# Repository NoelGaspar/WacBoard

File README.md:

# WacBoard
tesis based on wacboard v01

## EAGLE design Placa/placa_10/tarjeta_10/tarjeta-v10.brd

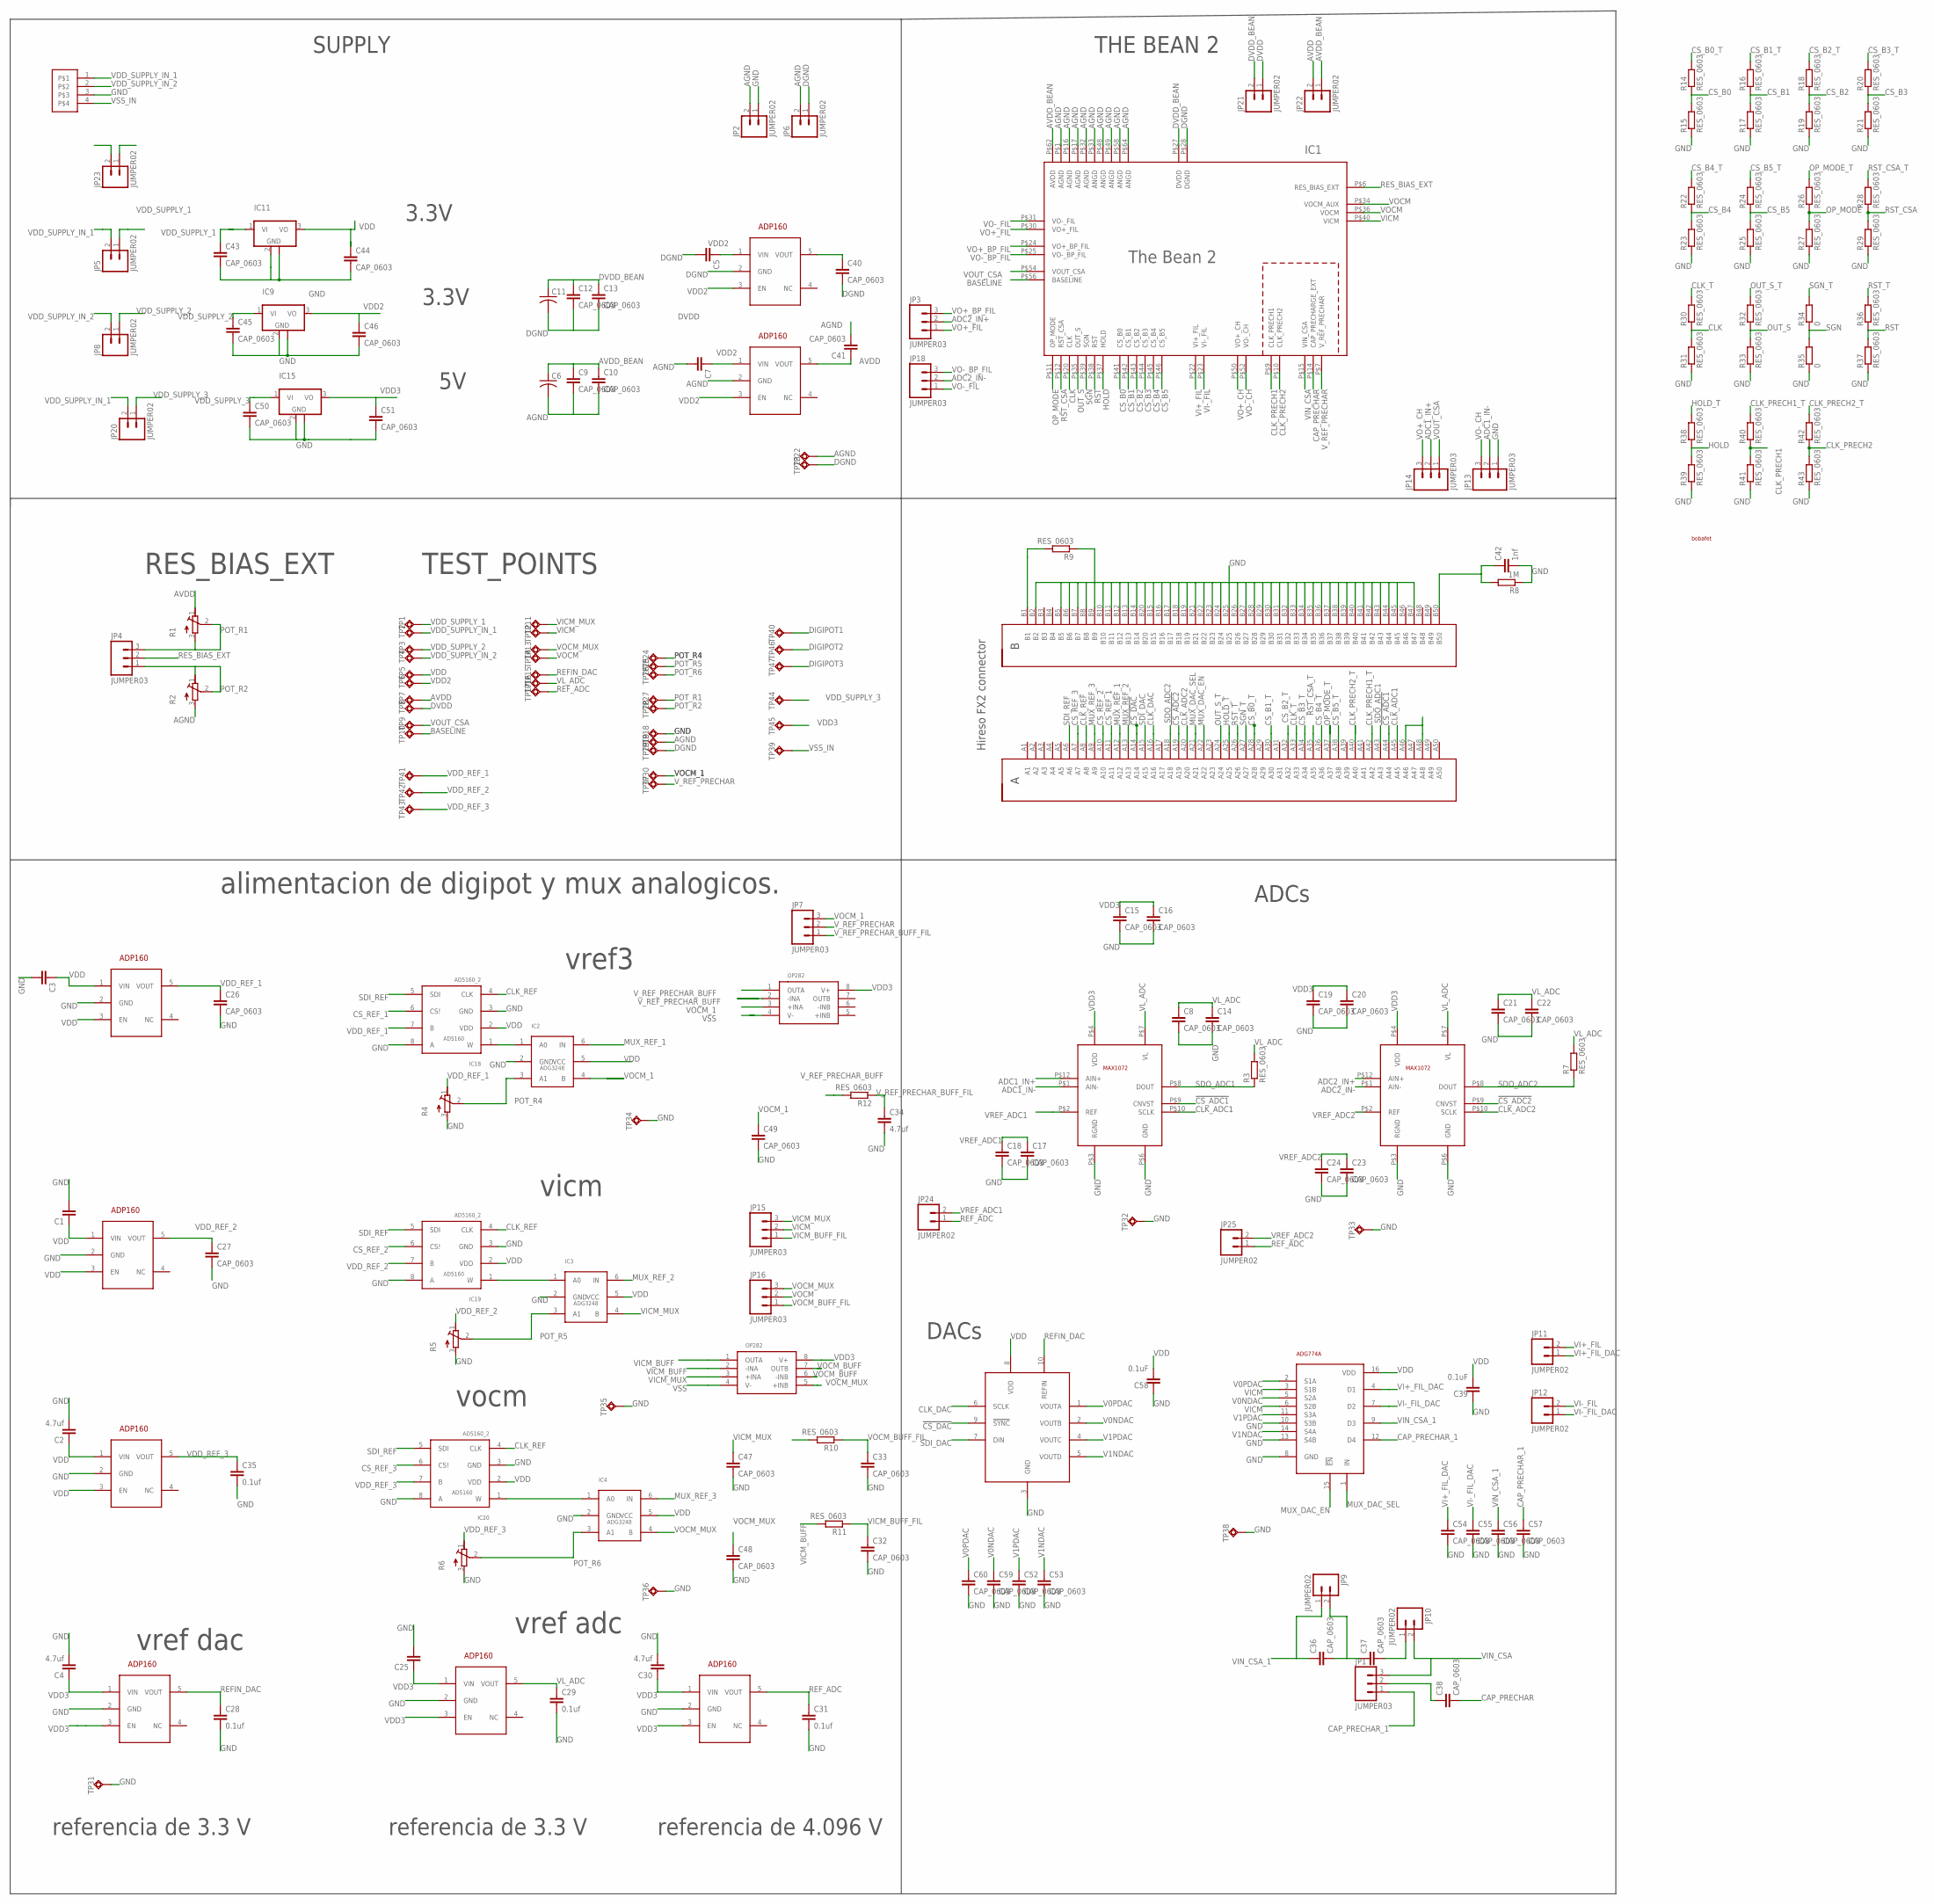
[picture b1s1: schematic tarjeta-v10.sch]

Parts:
C1, C3, C5, C7, C25: CAP_0402; C0402
C2, C4, C30: 4.7uf; C0402
C6, C11: CAP_0805; C0805
C8, C9, C10, C12, C13, C14, C15, C16, C17, C18, C19, C20, C21, C22, C23, C24, C26, C27, C32, C33, C36, C37, C38, C40, C41, C43, C44, C45, C46, C47, C48, C49, C50, C51, C52, C53, C54, C55, C56, C57, C59, C60: CAP_0603; C0603
C28, C29, C31, C35: 0.1uf; C0603
C34: 4.7uf; C0603
C39, C58: 0.1uF; C0603
C42: 1nf; C0603
IC1: THEBEAN2; CQFP64
IC2, IC3, IC4: ADG3248; SC70
IC5, IC6, IC7, IC8, IC10, IC13, IC16, IC17: ADP160; SOT23-5L_2
IC9, IC11, IC15: UA78M; SOT223
IC12, IC14: OP282; SOIC8
IC18, IC19, IC20: AD5160_2; SOT23-8_2
IC21: ADG774A; QSOP16
IC22, IC24: MAX1072; TQFN12
IC23: DAC7554; MSOP10
J1: HIRESO_FX_CONNECTOR; FX2-100S-1.27
JP1, JP3, JP4, JP7, JP13, JP14, JP15, JP16, JP18: JUMPER03; 1X03
JP2, JP5, JP6, JP8, JP9, JP10, JP11, JP12, JP20, JP21, JP22, JP23, JP24, JP25: JUMPER02; 1X02
JP17: JUMPER04; 1X04
R1, R2, R4, R5, R6: TRIMMER_ST5; ST-5EW
R3, R7, R9, R10, R11, R12, R14, R15, R16, R17, R18, R19, R20, R21, R22, R23, R24, R25, R26, R27, R28, R29, R30, R31, R32, R33, R36, R37, R38, R39, R40, R41, R42, R43: RES_0603; R0603
R8: 1M; R0603
R34, R35: 0; R0603
TP1, TP2, TP3, TP4, TP5, TP6, TP7, TP8, TP9, TP10, TP11, TP12, TP13, TP14, TP15, TP16, TP17, TP18, TP19, TP22, TP23, TP24, TP25, TP26, TP27, TP28, TP29, TP30, TP31, TP32, TP33, TP34, TP35, TP36, TP37, TP38, TP39, TP40, TP41, TP42, TP43, TP44, TP45, TP46, TP47: TEST_POINT; TP
U$1: LOGO

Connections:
!CS_ADC1: IC22.P$9 (CNVST), J1.A44
!CS_ADC2: IC24.P$9 (CNVST), J1.A19
!CS_DAC: IC23.9 (!SYNC), J1.A14
ADC1_IN+: IC22.P$12 (AIN+), JP14.2
ADC1_IN-: IC22.P$1 (AIN-), JP13.2
ADC2_IN+: IC24.P$12 (AIN+), JP3.2
ADC2_IN-: IC24.P$1 (AIN-), JP18.2
AGND: C6.2, C7.2, C9.2, C10.2, C41.2, IC1.P$1 (AGND), IC1.P$16 (AGND), IC1.P$17 (AGND), IC1.P$32 (AGND), IC1.P$33 (ANGD), IC1.P$48 (ANGD), IC1.P$49 (ANGD), IC1.P$58 (ANGD), IC1.P$64 (ANGD), IC13.2 (GND), JP2.2, JP6.2, R2.3, TP19.TP, TP22.TP
AVDD: C41.1, IC13.5 (VOUT), JP22.2, R1.1, TP7.TP
AVDD_BEAN: C6.1, C9.1, C10.1, IC1.P$62 (AVDD), JP22.1
BASELINE: IC1.P$56 (BASELINE), TP10.TP
CAP_PRECHAR: C38.2, IC1.P$14 (CAP_PRECHARGE_EXT)
CAP_PRECHAR_1: C57.1, IC21.12 (D4), JP1.1
CLK: IC1.P$20 (CLK), R30.1, R31.2
CLK_ADC1: IC22.P$10 (SCLK), J1.A45
CLK_ADC2: IC24.P$10 (SCLK), J1.A20
CLK_DAC: IC23.6 (SCLK), J1.A16
CLK_PRECH1: IC1.P$9 (CLK_PRECH1), R40.1, R41.2
CLK_PRECH1_T: J1.A42, R40.2
CLK_PRECH2: IC1.P$10 (CLK_PRECH2), R42.1, R43.2
CLK_PRECH2_T: J1.A40, R42.2
CLK_REF: IC18.4 (CLK), IC19.4 (CLK), IC20.4 (CLK), J1.A8
CLK_T: J1.A33, R30.2
CS_B0: IC1.P$41 (CS_B0), R14.1, R15.2
CS_B0_T: J1.A28, R14.2
CS_B1: IC1.P$42 (CS_B1), R16.1, R17.2
CS_B1_T: J1.A30, R16.2
CS_B2: IC1.P$43 (CS_B2), R18.1, R19.2
CS_B2_T: J1.A32, R18.2
CS_B3: IC1.P$44 (CS_B3), R20.1, R21.2
CS_B3_T: J1.A34, R20.2
CS_B4: IC1.P$45 (CS_B4), R22.1, R23.2
CS_B4_T: J1.A36, R22.2
CS_B5: IC1.P$46 (CS_B5), R24.1, R25.2
CS_B5_T: J1.A38, R24.2
CS_REF_1: IC18.6 (CS!), J1.A11
CS_REF_2: IC19.6 (CS!), J1.A10
CS_REF_3: IC20.6 (CS!), J1.A7
DGND: C5.2, C11.2, C12.2, C13.2, C40.2, IC1.P$28 (DGND), IC10.2 (GND), JP6.1, TP23.TP, TP29.TP
DIGIPOT1: IC2.1 (A0), IC18.1 (W), TP40.TP
DIGIPOT2: IC3.1 (A0), IC19.1 (W), TP46.TP
DIGIPOT3: IC4.1 (A0), IC20.1 (W), TP47.TP
DVDD: C40.1, IC10.5 (VOUT), JP21.1, TP8.TP
DVDD_BEAN: C11.1, C12.1, C13.1, IC1.P$27 (DVDD), JP21.2
GND: C1.2, C2.2, C3.2, C4.2, C8.2, C14.2, C15.2, C16.2, C17.2, C18.2, C19.2, C20.2, C21.2, C22.2, C23.2, C24.2, C25.2, C26.2, C27.2, C28.2, C29.2, C30.2, C31.2, C32.2, C33.2, C34.2, C35.2, C39.1, C42.2, C43.2, C44.2, C45.2, C46.2, C47.2, C48.2, C49.2, C50.2, C51.2, C52.2, C53.2, C54.2, C55.2, C56.2, C57.2, C58.1, C59.2, C60.2, IC2.2 (GND), IC3.2 (GND), IC4.2 (GND), IC5.2 (GND), IC6.2 (GND), IC7.2 (GND), IC8.2 (GND), IC9.2 (GND), IC9.4 (GND), IC11.2 (GND), IC11.4 (GND), IC15.2 (GND), IC15.4 (GND), IC16.2 (GND), IC17.2 (GND), IC18.3 (GND), IC18.8 (A), IC19.3 (GND), IC19.8 (A), IC20.3 (GND), IC20.8 (A), IC21.8 (GND), IC21.10 (S3B), IC21.13 (S4B), IC22.P$3 (RGND), IC22.P$6 (GND), IC23.3 (GND), IC24.P$3 (RGND), IC24.P$6 (GND), J1.B2, J1.B5, J1.B6, J1.B7, J1.B8, J1.B9, J1.B10, J1.B11, J1.B12, J1.B13, J1.B14, J1.B15, J1.B16, J1.B17, J1.B18, J1.B19, J1.B20, J1.B21, J1.B22, J1.B23, J1.B24, J1.B25, J1.B26, J1.B27, J1.B28, J1.B29, J1.B30, J1.B31, J1.B32, J1.B33, J1.B34, J1.B35, J1.B36, J1.B37, J1.B38, J1.B39, J1.B40, J1.B41, J1.B42, J1.B43, J1.B44, J1.B45, J1.B47, JP2.1, JP13.1, JP17.3, R4.3, R5.3, R6.3, R8.1, R9.1, R15.1, R17.1, R19.1, R21.1, R23.1, R25.1, R27.1, R29.1, R31.1, R33.1, R35.1, R37.1, R39.1, R41.1, R43.1, TP18.TP, TP31.TP, TP32.TP, TP33.TP, TP34.TP, TP35.TP, TP36.TP, TP38.TP
HOLD: IC1.P$37 (HOLD), R38.1, R39.2
HOLD_T: J1.A25, R38.2
MUX_DAC_EN: IC21.15 (!EN), J1.A22
MUX_DAC_SEL: IC21.1 (IN), J1.A21
MUX_REF_1: IC2.6 (IN), J1.A12
MUX_REF_2: IC3.6 (IN), J1.A13
MUX_REF_3: IC4.6 (IN), J1.A9
unnamed: C36.2, C37.1, JP9.2
unnamed: J1.B1, R9.2
unnamed: C37.2, JP10.1
unnamed: J1.A46, J1.A48
unnamed: C38.1, JP1.2
unnamed: C42.1, J1.B50, R8.2
OP_MODE: IC1.P$11 (OP_MODE), R26.1, R27.2
OP_MODE_T: J1.A37, R26.2
OUT_S: IC1.P$35 (OUT_S), R32.1, R33.2
OUT_S_T: J1.A24, R32.2
POT_R1: JP4.3, R1.2, R1.3, TP27.TP
POT_R2: JP4.1, R2.1, R2.2, TP28.TP
POT_R4: IC2.3 (A1), R4.2, TP24.TP
POT_R5: IC3.3 (A1), R5.2, TP25.TP
POT_R6: IC4.3 (A1), R6.2, TP26.TP
REFIN_DAC: C28.1, IC8.5 (VOUT), IC23.10 (REFIN), TP15.TP
REF_ADC: C31.1, IC17.5 (VOUT), JP24.1, JP25.1, TP17.TP
RES_BIAS_EXT: IC1.P$6 (RES_BIAS_EXT), JP4.2
RST: IC1.P$38 (RST), R36.1, R37.2
RST_CSA: IC1.P$12 (RST_CSA), R28.1, R29.2
RST_CSA_T: J1.A35, R28.2
RST_T: J1.A26, R36.2
SDI_DAC: IC23.7 (DIN), J1.A15
SDI_REF: IC18.5 (SDI), IC19.5 (SDI), IC20.5 (SDI), J1.A6
SDO_ADC1: IC22.P$8 (DOUT), J1.A43, R3.1
SDO_ADC2: IC24.P$8 (DOUT), J1.A18, R7.1
SGN: IC1.P$39 (SGN), R34.1, R35.2
SGN_T: J1.A27, R34.2
V0NDAC: C59.1, IC21.5 (S2A), IC23.2 (VOUTB)
V0PDAC: C60.1, IC21.2 (S1A), IC23.1 (VOUTA)
V1NDAC: C53.1, IC21.14 (S4A), IC23.5 (VOUTD)
V1PDAC: C52.1, IC21.11 (S3A), IC23.4 (VOUTC)
VDD: C1.1, C2.1, C3.1, C39.2, C44.1, C58.2, IC2.5 (VCC), IC3.5 (VCC), IC4.5 (VCC), IC5.1 (VIN), IC5.3 (EN), IC6.1 (VIN), IC6.3 (EN), IC7.1 (VIN), IC7.3 (EN), IC11.3 (VO), IC18.2 (VDD), IC19.2 (VDD), IC20.2 (VDD), IC21.16 (VDD), IC23.8 (VDD), TP5.TP
VDD2: C5.1, C7.1, C46.1, IC9.3 (VO), IC10.1 (VIN), IC10.3 (EN), IC13.1 (VIN), IC13.3 (EN), TP6.TP
VDD3: C4.1, C15.1, C16.1, C19.1, C20.1, C25.1, C30.1, C51.1, IC8.1 (VIN), IC8.3 (EN), IC12.8 (V+), IC14.8 (V+), IC15.3 (VO), IC16.1 (VIN), IC16.3 (EN), IC17.1 (VIN), IC17.3 (EN), IC22.P$4 (VDD), IC24.P$4 (VDD), TP45.TP
VDD_REF_1: C26.1, IC5.5 (VOUT), IC18.7 (B), R4.1, TP41.TP
VDD_REF_2: C27.1, IC6.5 (VOUT), IC19.7 (B), R5.1, TP42.TP
VDD_REF_3: C35.1, IC7.5 (VOUT), IC20.7 (B), R6.1, TP43.TP
VDD_SUPPLY_1: C43.1, IC11.1 (VI), JP5.1, TP1.TP
VDD_SUPPLY_2: C45.1, IC9.1 (VI), JP8.1, TP3.TP
VDD_SUPPLY_3: C50.1, IC15.1 (VI), JP20.1, TP44.TP
VDD_SUPPLY_IN_1: JP5.2, JP17.1, JP20.2, TP2.TP
VDD_SUPPLY_IN_2: JP8.2, JP17.2, TP4.TP
VI+_FIL: IC1.P$22 (VI+_FIL), JP11.2
VI+_FIL_DAC: C54.1, IC21.4 (D1), JP11.1
VI-_FIL: IC1.P$23 (VI-_FIL), JP12.2
VI-_FIL_DAC: C55.1, IC21.7 (D2), JP12.1
VICM: IC1.P$40 (VICM), IC21.3 (S1B), IC21.6 (S2B), JP15.2, TP12.TP
VICM_BUFF: IC12.1 (OUTA), IC12.2 (-INA), R11.2
VICM_BUFF_FIL: C32.1, JP15.1, R11.1
VICM_MUX: C47.1, IC3.4 (B), IC12.3 (+INA), JP15.3, TP11.TP
VIN_CSA: IC1.P$15 (VIN_CSA), JP1.3, JP10.2
VIN_CSA_1: C36.1, C56.1, IC21.9 (D3), JP9.1
VL_ADC: C8.1, C14.1, C21.1, C22.1, C29.1, IC16.5 (VOUT), IC22.P$7 (VL), IC24.P$7 (VL), R3.2, R7.2, TP16.TP
VO+_BP_FIL: IC1.P$24 (VO+_BP_FIL), JP3.3
VO+_CH: IC1.P$50 (VO+_CH), JP14.3
VO+_FIL: IC1.P$30 (VO+_FIL), JP3.1
VO-_BP_FIL: IC1.P$25 (VO-_BP_FIL), JP18.3
VO-_CH: IC1.P$52 (VO-_CH), JP13.3
VO-_FIL: IC1.P$31 (VO-_FIL), JP18.1
VOCM: IC1.P$34 (VOCM_AUX), IC1.P$36 (VOCM), JP16.2, TP14.TP
VOCM_1: C49.1, IC2.4 (B), IC14.3 (+INA), JP7.3, TP30.TP
VOCM_BUFF: IC12.6 (-INB), IC12.7 (OUTB), R10.2
VOCM_BUFF_FIL: C33.1, JP16.1, R10.1
VOCM_MUX: C48.1, IC4.4 (B), IC12.5 (+INB), JP16.3, TP13.TP
VOUT_CSA: IC1.P$54 (VOUT_CSA), JP14.1, TP9.TP
VREF_ADC1: C17.1, C18.1, IC22.P$2 (REF), JP24.2
VREF_ADC2: C23.1, C24.1, IC24.P$2 (REF), JP25.2
VSS: IC12.4 (V-), IC14.4 (V-), JP23.1
VSS_IN: JP17.4, JP23.2, TP39.TP
V_REF_PRECHAR: IC1.P$7 (V_REF_PRECHAR), JP7.2, TP37.TP
V_REF_PRECHAR_BUFF: IC14.1 (OUTA), IC14.2 (-INA), R12.2
V_REF_PRECHAR_BUFF_FIL: C34.1, JP7.1, R12.1

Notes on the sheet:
vicm
vocm
alimentacion de digipot y mux analogicos.
RES_BIAS_EXT
ADCs
SUPPLY
THE BEAN 2
DACs
TEST_POINTS
vref3
vref adc
vref dac
referencia de 3.3 V
referencia de 4.096 V
3.3V

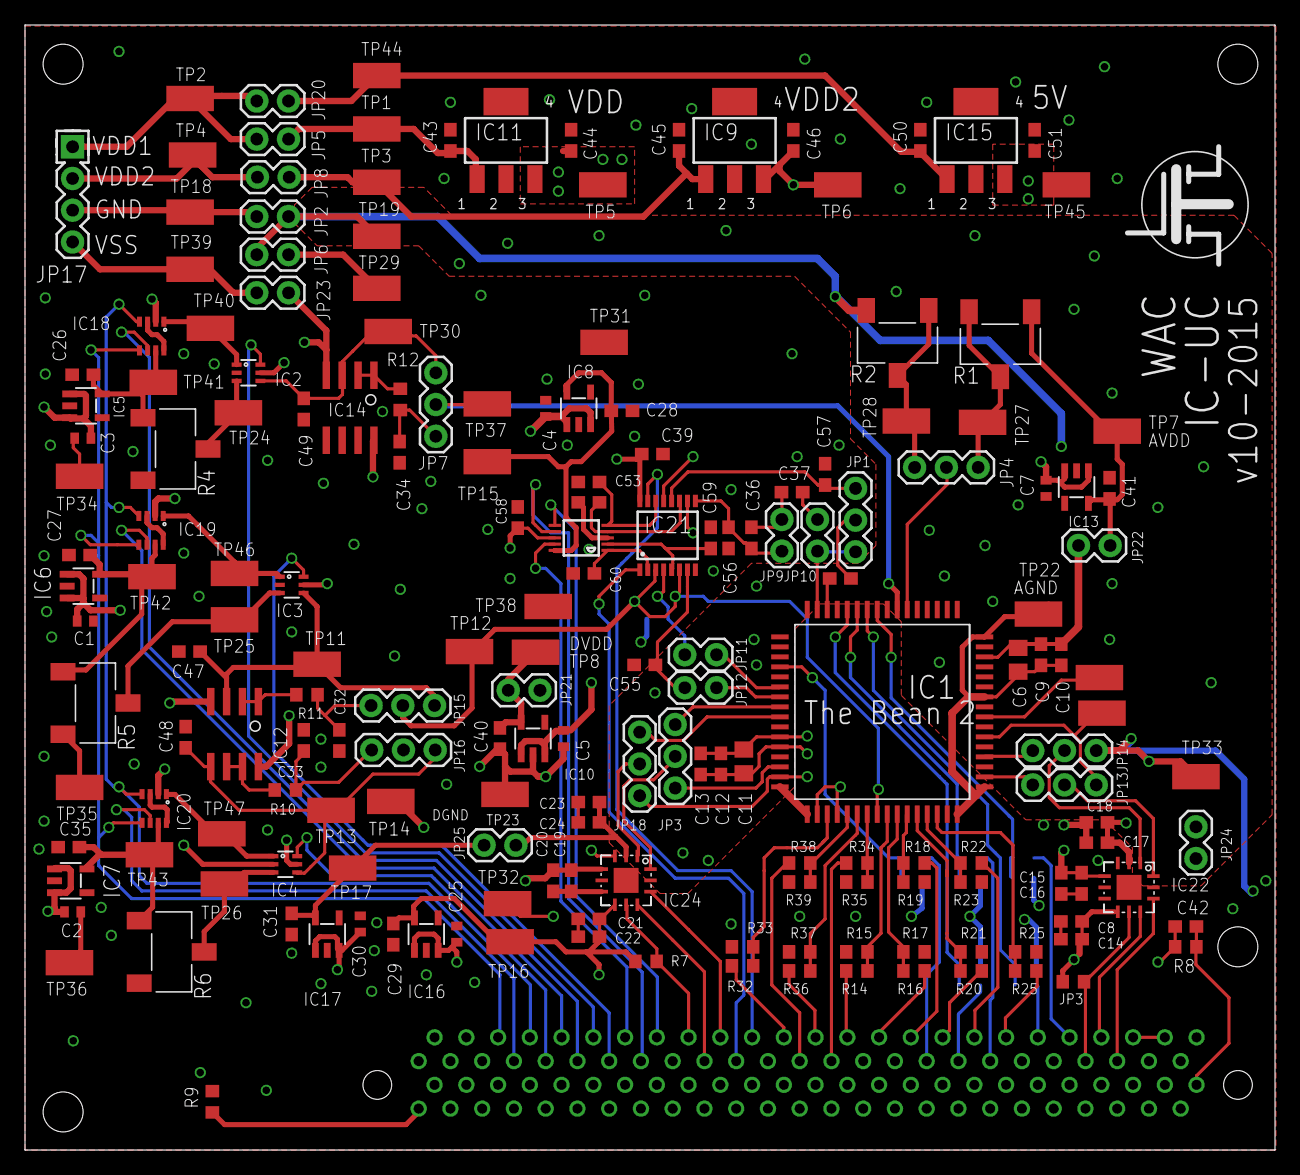
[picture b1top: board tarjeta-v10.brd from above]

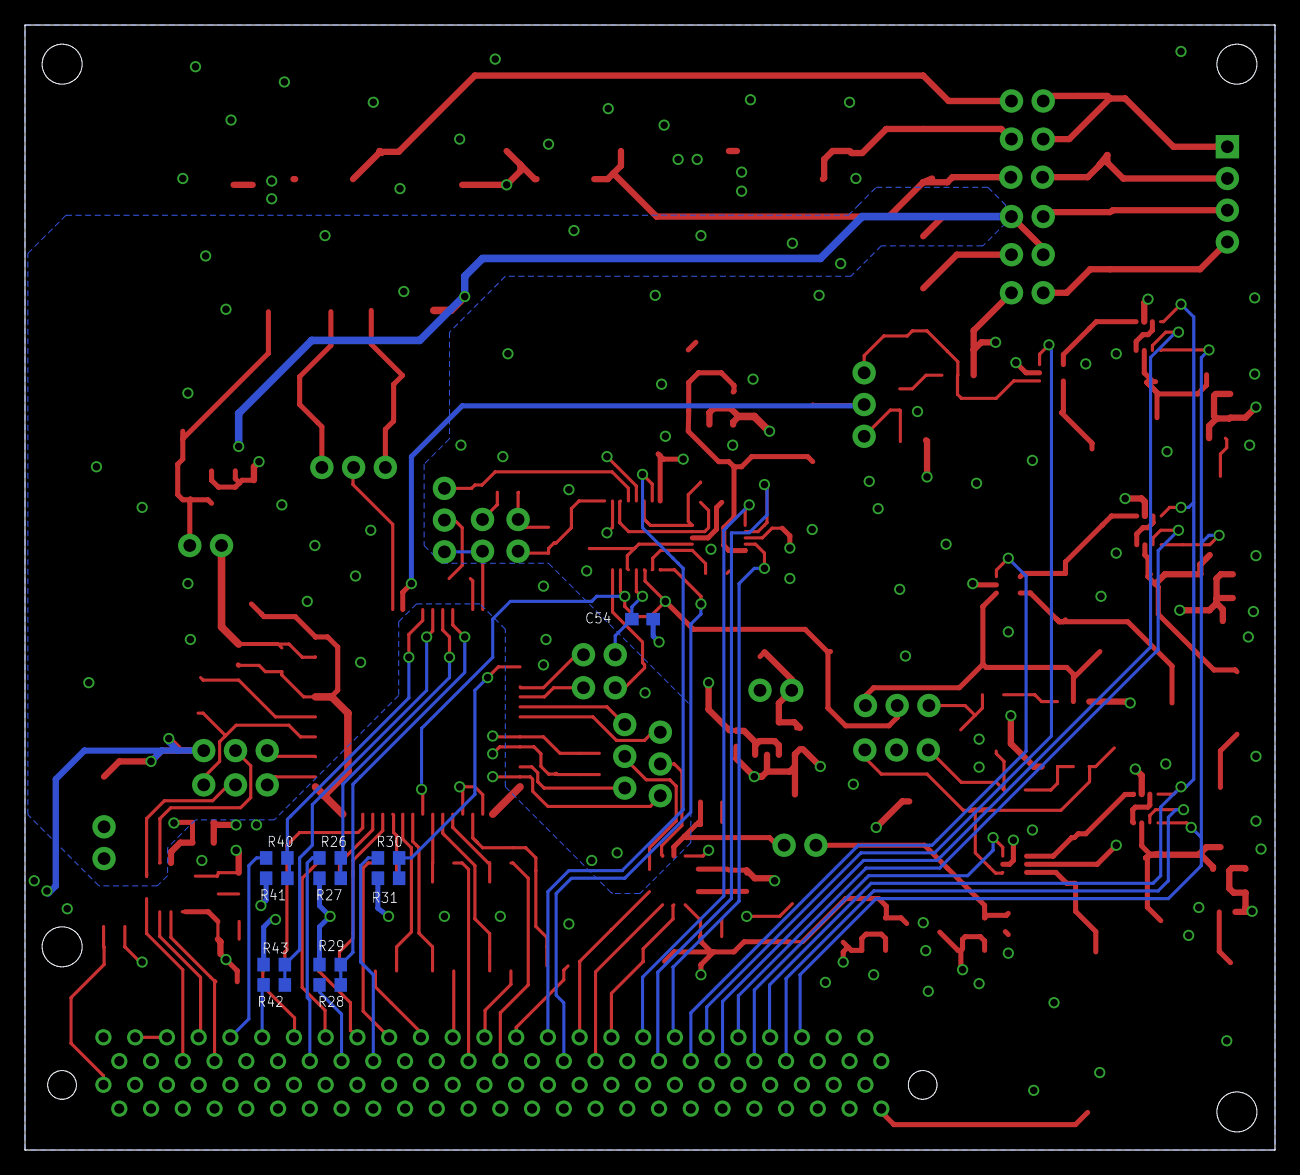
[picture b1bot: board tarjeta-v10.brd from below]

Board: 4 copper layers, 100.0 x 90.0 mm, 197 parts (11 on the bottom side), 125 nets.

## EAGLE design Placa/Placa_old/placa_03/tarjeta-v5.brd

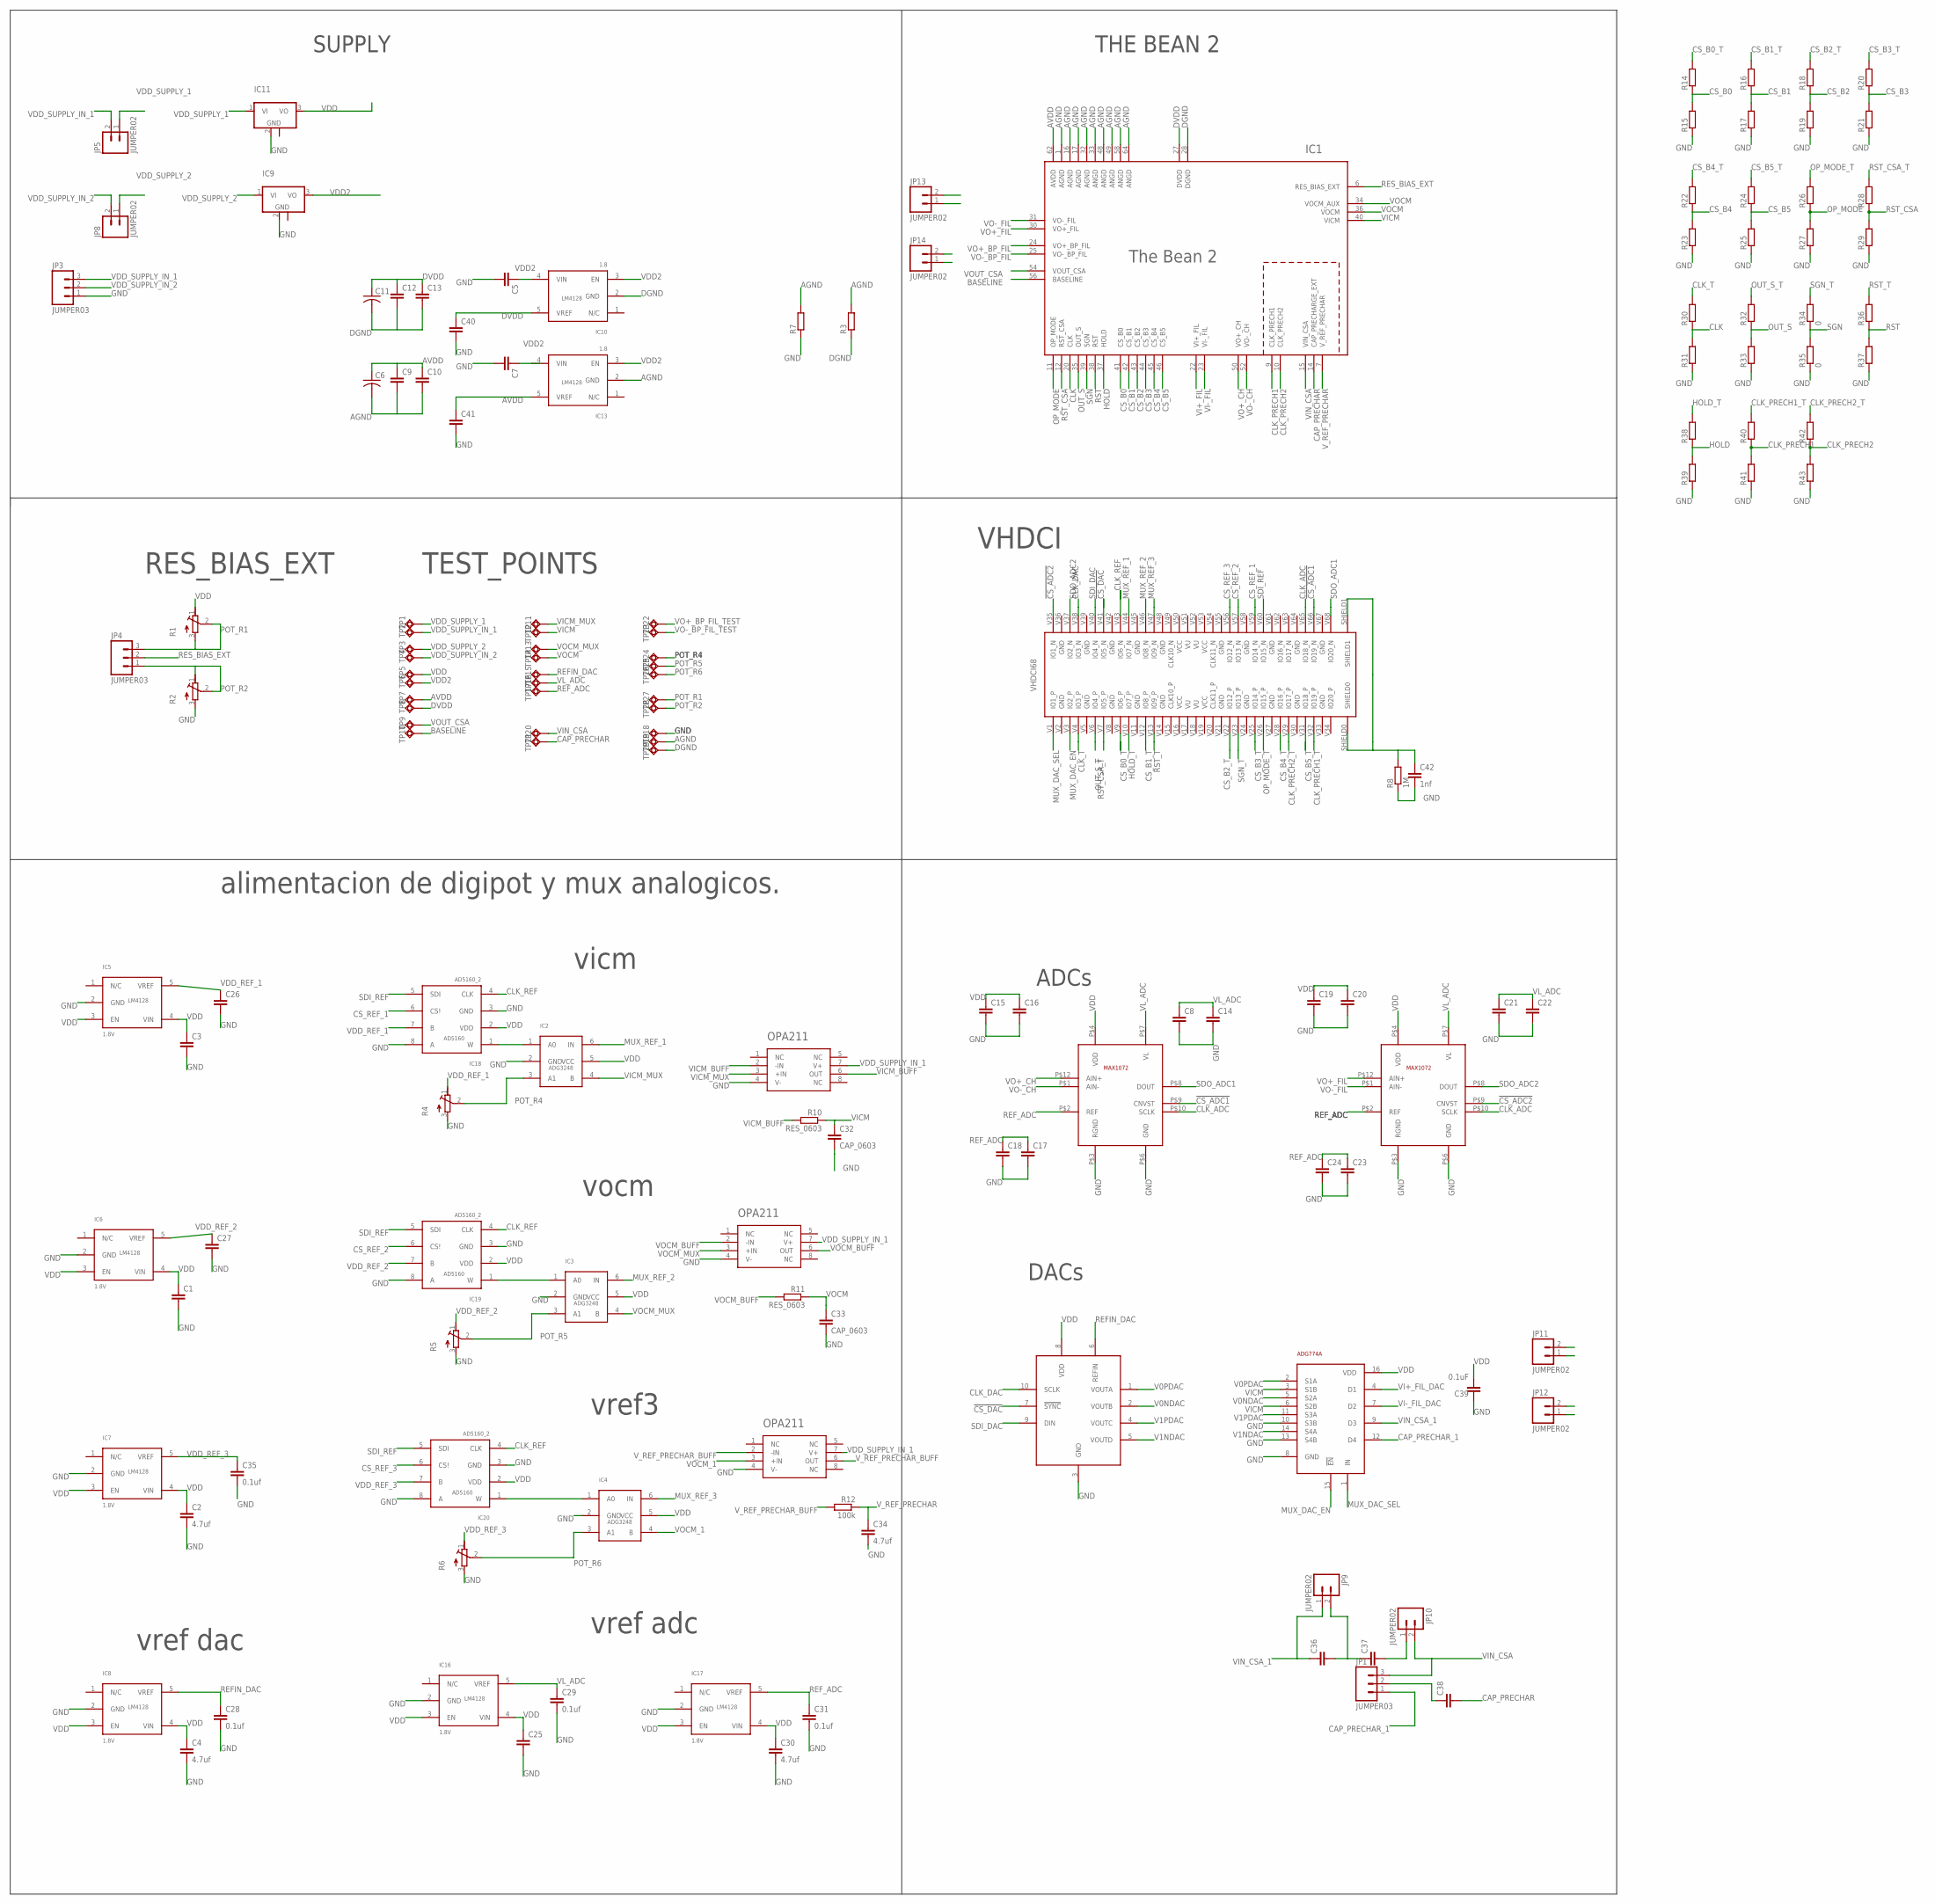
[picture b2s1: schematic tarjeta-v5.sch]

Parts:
C1, C3, C5, C7, C8, C9, C10, C12, C13, C14, C15, C16, C17, C18, C19, C20, C21, C22, C23, C24, C25, C26, C27, C36, C37, C38, C40, C41: CAP_0402; C0402
C2, C4, C30: 4.7uf; C0402
C6, C11: CAP_0805; C0805
C28, C29, C31, C35: 0.1uf; C0402
C32, C33: CAP_0603; C0603
C34: 4.7uf; C0603
C39: 0.1uF; C0402
C42: 1nf; C0402
IC1: THE_BEAN_2; QFN64
IC2, IC3, IC4: ADG3248; SC70
IC5, IC6, IC7, IC8, IC16, IC17: 1.8V; SOT23-5L_2
IC9, IC11: UA78M33DCY; SOT223
IC10, IC13: 1.8; SOT23-5L_2
IC12, IC14, IC15: OPA211; SOIC8
IC18, IC19, IC20: AD5160_2; SOT23-8_2
IC21: ADG774A; QSOP16
IC22: MAX1072; TQFN12
IC23: DAC7554; MSOP10
JP1, JP3, JP4: JUMPER03; 1X03
JP5, JP8, JP9, JP10, JP11, JP12, JP13, JP14: JUMPER02; 1X02
R1, R2, R4, R5, R6: TRIMMER_ST5; ST-5EW
R3, R7: RES_0402; R0402
R8: 1M; R0402
R10, R11: RES_0603; R0603
R12: 100k; R0603
R14, R15, R16, R17, R18, R19, R20, R21, R22, R23, R24, R25, R26, R27, R28, R29, R30, R31, R32, R33, R36, R37, R38, R39, R40, R41, R42, R43: R-EU_R0402; R0402@1
R34, R35: 0; R0402@1
TP1, TP2, TP3, TP4, TP5, TP6, TP7, TP8, TP9, TP10, TP11, TP12, TP13, TP14, TP15, TP16, TP17, TP18, TP19, TP20, TP21, TP22, TP23, TP24, TP25, TP26, TP27, TP28, TP29: TEST_POINT; TP
U$2: VHDCI68
U$5: MAX1072; TQFN12

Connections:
!CS_ADC1: IC22.P$9 (CNVST), U$2.V66 (IO19_N)
!CS_ADC2: U$2.V35 (IO1_N), U$5.P$9 (CNVST)
!CS_DAC: IC23.7 (!SYNC), U$2.V41 (IO5_N)
AGND: C6.2, C9.2, C10.2, IC1.1 (AGND), IC1.16 (AGND), IC1.17 (AGND), IC1.32 (AGND), IC1.33 (ANGD), IC1.48 (ANGD), IC1.49 (ANGD), IC1.58 (ANGD), IC1.64 (ANGD), IC13.2 (GND), R3.2, R7.2, TP19.TP
AVDD: C6.1, C9.1, C10.1, C41.1, IC1.62 (AVDD), IC13.5 (VREF), TP7.TP
BASELINE: IC1.56 (BASELINE), TP10.TP
CAP_PRECHAR: C38.2, IC1.14 (CAP_PRECHARGE_EXT), TP21.TP
CAP_PRECHAR_1: IC21.12 (D4), JP1.1
CLK: IC1.20 (CLK), R30.1, R31.2
CLK_ADC: IC22.P$10 (SCLK), U$2.V65 (IO18_N), U$5.P$10 (SCLK)
CLK_DAC: IC23.10 (SCLK), U$2.V38 (IO3_N)
CLK_PRECH1: IC1.9 (CLK_PRECH1), R40.1, R41.2
CLK_PRECH1_T: R40.2, U$2.V32 (IO19_P)
CLK_PRECH2: IC1.10 (CLK_PRECH2), R42.1, R43.2
CLK_PRECH2_T: R42.2, U$2.V29 (IO17_P)
CLK_REF: IC18.4 (CLK), IC19.4 (CLK), IC20.4 (CLK), U$2.V43 (IO6_N)
CLK_T: R30.2, U$2.V4 (IO3_P)
CS_B0: IC1.41 (CS_B0), R14.1, R15.2
CS_B0_T: R14.2, U$2.V9 (IO6_P)
CS_B1: IC1.42 (CS_B1), R16.1, R17.2
CS_B1_T: R16.2, U$2.V12 (IO8_P)
CS_B2: IC1.43 (CS_B2), R18.1, R19.2
CS_B2_T: R18.2, U$2.V22 (IO12_P)
CS_B3: IC1.44 (CS_B3), R20.1, R21.2
CS_B3_T: R20.2, U$2.V25 (IO14_P)
CS_B4: IC1.45 (CS_B4), R22.1, R23.2
CS_B4_T: R22.2, U$2.V28 (IO16_P)
CS_B5: IC1.46 (CS_B5), R24.1, R25.2
CS_B5_T: R24.2, U$2.V31 (IO18_P)
CS_REF_1: IC18.6 (CS!), U$2.V59 (IO14_N)
CS_REF_2: IC19.6 (CS!), U$2.V57 (IO13_N)
CS_REF_3: IC20.6 (CS!), U$2.V56 (IO12_N)
DGND: C11.2, C12.2, C13.2, IC1.28 (DGND), IC10.2 (GND), R3.1, TP29.TP
DVDD: C11.1, C12.1, C13.1, C40.1, IC1.27 (DVDD), IC10.5 (VREF), TP8.TP
GND: C1.2, C2.2, C3.2, C4.2, C5.2, C7.2, C8.2, C14.2, C15.2, C16.2, C17.2, C18.2, C19.2, C20.2, C21.2, C22.2, C23.2, C24.2, C25.2, C26.2, C27.2, C28.2, C29.2, C30.2, C31.2, C32.2, C33.2, C34.2, C35.2, C39.1, C40.2, C41.2, C42.2, IC2.2 (GND), IC3.2 (GND), IC4.2 (GND), IC5.2 (GND), IC6.2 (GND), IC7.2 (GND), IC8.2 (GND), IC9.2 (GND), IC11.2 (GND), IC12.4 (V-), IC14.4 (V-), IC15.4 (V-), IC16.2 (GND), IC17.2 (GND), IC18.3 (GND), IC18.8 (A), IC19.3 (GND), IC19.8 (A), IC20.3 (GND), IC20.8 (A), IC21.8 (GND), IC21.10 (S3B), IC21.13 (S4B), IC22.P$3 (RGND), IC22.P$6 (GND), IC23.3 (GND), JP3.1, R2.3, R4.3, R5.3, R6.3, R7.1, R8.1, R15.1, R17.1, R19.1, R21.1, R23.1, R25.1, R27.1, R29.1, R31.1, R33.1, R35.1, R37.1, R39.1, R41.1, R43.1, TP18.TP, U$5.P$3 (RGND), U$5.P$6 (GND)
HOLD: IC1.37 (HOLD), R38.1, R39.2
HOLD_T: R38.2, U$2.V10 (IO7_P)
MUX_DAC_EN: IC21.15 (!EN), U$2.V3 (IO2_P)
MUX_DAC_SEL: IC21.1 (IN), U$2.V1 (IO1_P)
MUX_REF_1: IC2.6 (IN), U$2.V44 (IO7_N)
MUX_REF_2: IC3.6 (IN), U$2.V46 (IO8_N)
MUX_REF_3: IC4.6 (IN), U$2.V47 (IO9_N)
unnamed: C36.2, C37.1, JP9.2
unnamed: C37.2, JP10.1
unnamed: IC4.1 (A0), IC20.1 (W)
unnamed: C38.1, JP1.2
unnamed: C42.1, R8.2, U$2.SHIELD0, U$2.SHIELD1
unnamed: IC2.1 (A0), IC18.1 (W)
unnamed: IC3.1 (A0), IC19.1 (W)
OP_MODE: IC1.11 (OP_MODE), R26.1, R27.2
OP_MODE_T: R26.2, U$2.V26 (IO15_P)
OUT_S: IC1.35 (OUT_S), R32.1, R33.2
OUT_S_T: R32.2, U$2.V6 (IO4_P)
POT_R1: JP4.3, R1.2, R1.3, TP27.TP
POT_R2: JP4.1, R2.1, R2.2, TP28.TP
POT_R4: IC2.3 (A1), R4.2, TP24.TP
POT_R5: IC3.3 (A1), R5.2, TP25.TP
POT_R6: IC4.3 (A1), R6.2, TP26.TP
REFIN_DAC: C28.1, IC8.5 (VREF), IC23.6 (REFIN), TP15.TP
REF_ADC: C17.1, C18.1, C23.1, C24.1, C31.1, IC17.5 (VREF), IC22.P$2 (REF), TP17.TP, U$5.P$2 (REF)
RES_BIAS_EXT: IC1.6 (RES_BIAS_EXT), JP4.2
RST: IC1.38 (RST), R36.1, R37.2
RST_CSA: IC1.12 (RST_CSA), R28.1, R29.2
RST_CSA_T: R28.2, U$2.V7 (IO5_P)
RST_T: R36.2, U$2.V13 (IO9_P)
SDI_DAC: IC23.9 (DIN), U$2.V40 (IO4_N)
SDI_REF: IC18.5 (SDI), IC19.5 (SDI), IC20.5 (SDI), U$2.V60 (IO15_N)
SDO_ADC1: IC22.P$8 (DOUT), U$2.V68 (IO20_N)
SDO_ADC2: U$2.V37 (IO2_N), U$5.P$8 (DOUT)
SGN: IC1.39 (SGN), R34.1, R35.2
SGN_T: R34.2, U$2.V23 (IO13_P)
V0NDAC: IC21.5 (S2A), IC23.2 (VOUTB)
V0PDAC: IC21.2 (S1A), IC23.1 (VOUTA)
V1NDAC: IC21.14 (S4A), IC23.5 (VOUTD)
V1PDAC: IC21.11 (S3A), IC23.4 (VOUTC)
VCC: U$2.V16 (VCC), U$2.V19 (VCC), U$2.V50 (VCC), U$2.V53 (VCC)
VDD: C1.1, C2.1, C3.1, C4.1, C15.1, C16.1, C19.1, C20.1, C25.1, C30.1, C39.2, IC2.5 (VCC), IC3.5 (VCC), IC4.5 (VCC), IC5.3 (EN), IC5.4 (VIN), IC6.3 (EN), IC6.4 (VIN), IC7.3 (EN), IC7.4 (VIN), IC8.3 (EN), IC8.4 (VIN), IC11.3 (VO), IC16.3 (EN), IC16.4 (VIN), IC17.3 (EN), IC17.4 (VIN), IC18.2 (VDD), IC19.2 (VDD), IC20.2 (VDD), IC21.16 (VDD), IC22.P$4 (VDD), IC23.8 (VDD), R1.1, TP5.TP, U$5.P$4 (VDD)
VDD2: C5.1, C7.1, IC9.3 (VO), IC10.3 (EN), IC10.4 (VIN), IC13.3 (EN), IC13.4 (VIN), TP6.TP
VDD_REF_1: C26.1, IC5.5 (VREF), IC18.7 (B), R4.1
VDD_REF_2: C27.1, IC6.5 (VREF), IC19.7 (B), R5.1
VDD_REF_3: C35.1, IC7.5 (VREF), IC20.7 (B), R6.1
VDD_SUPPLY_1: IC11.1 (VI), JP5.1, TP1.TP
VDD_SUPPLY_2: IC9.1 (VI), JP8.1, TP3.TP
VDD_SUPPLY_IN_1: IC12.7 (V+), IC14.7 (V+), IC15.7 (V+), JP3.3, JP5.2, TP2.TP
VDD_SUPPLY_IN_2: JP3.2, JP8.2, TP4.TP
VI+_FIL: IC1.22 (VI+_FIL), JP11.2
VI+_FIL_DAC: IC21.4 (D1), JP11.1
VI-_FIL: IC1.23 (VI-_FIL), JP12.2
VI-_FIL_DAC: IC21.7 (D2), JP12.1
VICM: C32.1, IC1.40 (VICM), IC21.3 (S1B), IC21.6 (S2B), R10.1, TP12.TP
VICM_BUFF: IC12.2 (-IN), IC12.6 (OUT), R10.2
VICM_MUX: IC2.4 (B), IC12.3 (+IN), TP11.TP
VIN_CSA: IC1.15 (VIN_CSA), JP1.3, JP10.2, TP20.TP
VIN_CSA_1: C36.1, IC21.9 (D3), JP9.1
VL_ADC: C8.1, C14.1, C21.1, C22.1, C29.1, IC16.5 (VREF), IC22.P$7 (VL), TP16.TP, U$5.P$7 (VL)
VO+_BP_FIL: IC1.24 (VO+_BP_FIL), JP13.1
VO+_BP_FIL_TEST: JP13.2, TP22.TP
VO+_CH: IC1.50 (VO+_CH), IC22.P$12 (AIN+)
VO+_FIL: IC1.30 (VO+_FIL), U$5.P$12 (AIN+)
VO-_BP_FIL: IC1.25 (VO-_BP_FIL), JP14.1
VO-_BP_FIL_TEST: JP14.2, TP23.TP
VO-_CH: IC1.52 (VO-_CH), IC22.P$1 (AIN-)
VO-_FIL: IC1.31 (VO-_FIL), U$5.P$1 (AIN-)
VOCM: C33.1, IC1.34 (VOCM_AUX), IC1.36 (VOCM), R11.1, TP14.TP
VOCM_1: IC4.4 (B), IC15.3 (+IN)
VOCM_BUFF: IC14.2 (-IN), IC14.6 (OUT), R11.2
VOCM_MUX: IC3.4 (B), IC14.3 (+IN), TP13.TP
VOUT_CSA: IC1.54 (VOUT_CSA), TP9.TP
VU: U$2.V17 (VU), U$2.V18 (VU), U$2.V51 (VU), U$2.V52 (VU)
V_REF_PRECHAR: C34.1, IC1.7 (V_REF_PRECHAR), R12.1
V_REF_PRECHAR_BUFF: IC15.2 (-IN), IC15.6 (OUT), R12.2

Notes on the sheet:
vicm
vocm
alimentacion de digipot y mux analogicos.
VHDCI
RES_BIAS_EXT
ADCs
SUPPLY
THE BEAN 2
DACs
TEST_POINTS
vref3
vref adc
vref dac
